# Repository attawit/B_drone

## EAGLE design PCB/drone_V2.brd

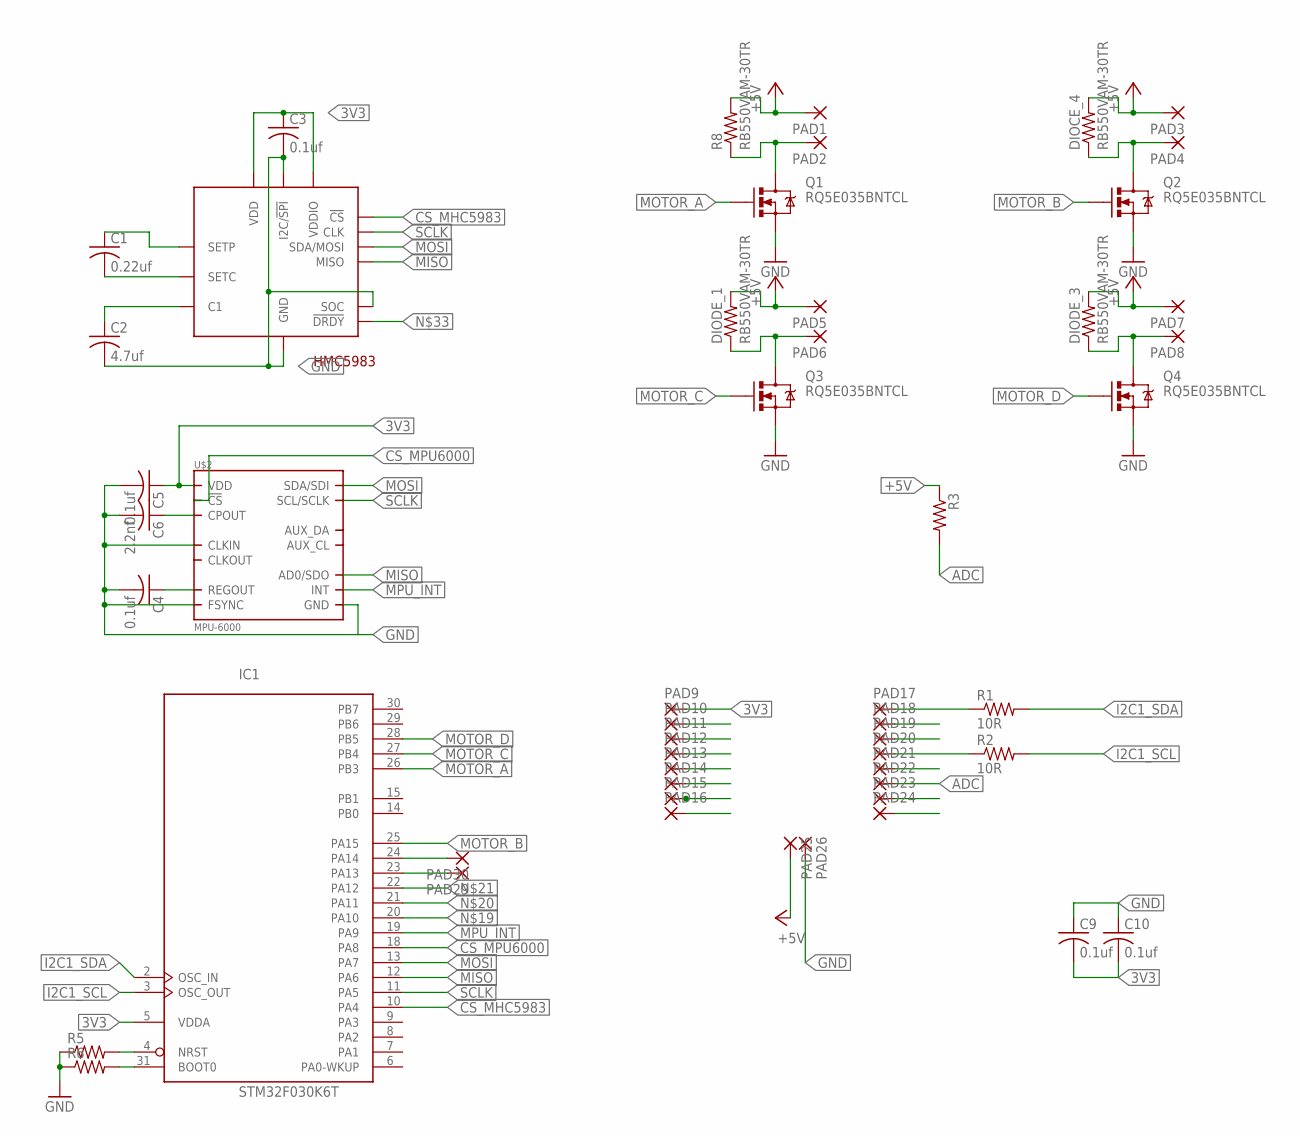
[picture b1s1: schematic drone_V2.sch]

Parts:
C1: 0.22uf; C0805K
C2: 4.7uf; C1206
C3, C4, C5, C9, C10: 0.1uf; C0805K
C6: 2.2nf; C0805K
DIOCE_4: RB550VAM-30TR; R0805
DIODE_1, DIODE_3: RB550VAM-30TR; R0805
HMC5983: HMC5983; LPCC16
IC1: STM32F030K6T; LQFP32
PAD1, PAD2, PAD3, PAD4, PAD5, PAD6, PAD7, PAD8: 1,6/0,8
PAD9, PAD10, PAD11, PAD12, PAD13, PAD14, PAD15, PAD16, PAD17, PAD18, PAD19, PAD20, PAD21, PAD22, PAD23, PAD24, PAD25, PAD26, PAD29, PAD30: 1,6/0,9
Q1, Q2, Q3, Q4: RQ5E035BNTCL; SOT23-3
R1, R2: 10R; R0805
R3, R5, R6: R-US_R0805; R0805
R8: RB550VAM-30TR; R0805
U$2: MPU-6000; QFN.24.4X4

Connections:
3V3: C3.1, C5.1, C9.2, C10.2, HMC5983.P$2 (VDD), HMC5983.P$13 (VDDIO), IC1.1 (VDD), IC1.5 (VDDA), IC1.17 (VDD), PAD9.1, U$2.13 (VDD)
+5V: DIOCE_4.2, DIODE_1.2, DIODE_3.2, PAD1.1, PAD3.1, PAD5.1, PAD7.1, PAD25.1, R3.1, R8.2
ADC: PAD22.1, R3.2
CS_MHC5983: HMC5983.P$4 (!CS), IC1.10 (PA4)
CS_MPU6000: IC1.18 (PA8), U$2.8 (!CS)
DIODE_2: PAD2.1, Q1.3 (D), R8.1
GND: C2.2, C3.2, C4.2, C5.2, C6.2, C9.1, C10.1, HMC5983.P$6 (I2C/!SPI), HMC5983.P$9 (SOC), HMC5983.P$11 (GND), IC1.16 (VSS), IC1.32 (VSS), PAD24.1, PAD26.1, Q1.2 (S), Q2.2 (S), Q3.2 (S), Q4.2 (S), R5.1, R6.1, U$2.1 (CLKIN), U$2.11 (FSYNC), U$2.18 (GND)
I2C1_SCL: IC1.3 (OSC_OUT), R2.2
I2C1_SDA: IC1.2 (OSC_IN), R1.2
MISO: HMC5983.P$5 (MISO), IC1.12 (PA6), U$2.9 (AD0/SDO)
MOSI: HMC5983.P$16 (SDA/MOSI), IC1.13 (PA7), U$2.24 (SDA/SDI)
MOTOR_A: IC1.26 (PB3), Q1.1 (G)
MOTOR_B: IC1.25 (PA15), Q2.1 (G)
MOTOR_C: IC1.27 (PB4), Q3.1 (G)
MOTOR_D: IC1.28 (PB5), Q4.1 (G)
MPU_INT: IC1.19 (PA9), U$2.12 (INT)
unnamed: DIODE_1.1, PAD6.1, Q3.3 (D)
unnamed: DIODE_3.1, PAD8.1, Q4.3 (D)
unnamed: DIOCE_4.1, PAD4.1, Q2.3 (D)
unnamed: IC1.4 (NRST), R5.2
unnamed: IC1.31 (BOOT0), R6.2
unnamed: C4.1, U$2.10 (REGOUT)
unnamed: PAD17.1, R1.1
unnamed: PAD20.1, R2.1
unnamed: IC1.23 (PA13), PAD29.1
unnamed: IC1.24 (PA14), PAD30.1
unnamed: C1.2, HMC5983.P$12 (SETC)
unnamed: C1.1, HMC5983.P$8 (SETP)
unnamed: C2.1, HMC5983.P$10 (C1)
unnamed: C6.1, U$2.20 (CPOUT)
SCLK: HMC5983.P$1 (CLK), IC1.11 (PA5), U$2.23 (SCL/SCLK)

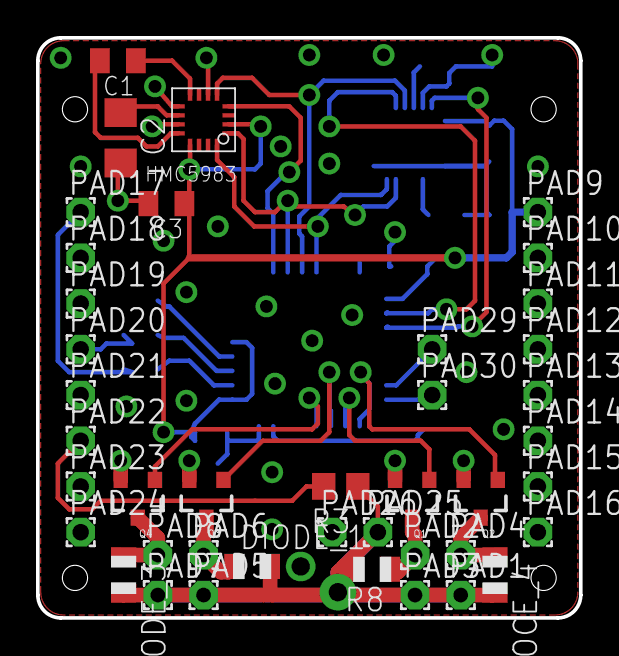
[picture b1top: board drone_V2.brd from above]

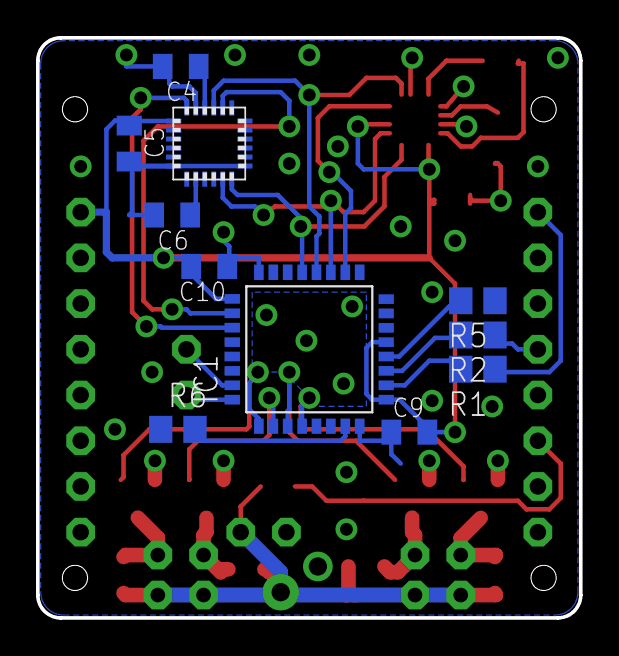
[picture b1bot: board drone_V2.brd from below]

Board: 2 copper layers, 30.2 x 32.2 mm, 52 parts (11 on the bottom side), 31 nets.

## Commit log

2016-03-12 first version

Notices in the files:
parts and their libraries:
SparkFun: Licensing: CC v3.0 Share-Alike You are welcome to use this library for commercial purposes.
